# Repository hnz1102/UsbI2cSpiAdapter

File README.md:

# USB-I2C/SPI Adapter

<div align="center">
  
</div>

## Overview

This directory contains the hardware design files for a USB-I2C/SPI adapter based on the FTDI FT232H chip. The adapter enables USB connectivity for I2C and SPI communication with various embedded devices and sensors.

## Hardware Features

- **USB Interface**: USB 2.0 Full Speed (12 Mbps)
- **Main Controller**: FTDI FT232H (MPSSE capable)
- **Protocols Supported**: I2C, SPI, GPIO
- **USB-C Connector**: Modern USB Type-C connection
- **Operating Voltage**: 3.3V I/O (5V USB powered)
- **Compact Design**: Optimized PCB layout for ease of use

## Design Files

This repository includes the following KiCad project files:

| File | Description |
|------|-------------|
| `i2cmaster.kicad_sch` | Schematic design file |
| `i2cmaster.kicad_pcb` | PCB layout file |
| `i2cmaster.kicad_pro` | KiCad project file |
| `i2cmaster.csv` | Bill of Materials (BOM) |
| `fp-lib-table` | Footprint library table |
| `Library.pretty/` | Custom footprint library |

## 3D Model

A 3D model of the enclosure is available:

- `F3D/usbi2c.f3d` - Fusion 360 design file for the adapter enclosure

## Production Files

The `i2cmaster.kicad_pcb_gerber.zip` is Gerber files and production data for PCB manufacturing.

## Key Components

- **FT232H**: FTDI USB-to-MPSSE bridge chip
- **USB-C Connector**: 5077CR-16-SMC2-BK-TR (USB Type-C receptacle)
- **Voltage Regulator**: 3.3V LDO for I/O interface
- **ESD Protection**: Protection circuitry for USB lines
- **Pull-up Resistors**: I2C bus pull-up resistors (typically 4.7kΩ)

## Pin Configuration

The adapter connector has the following pin assignments:

| Pin | Signal | Description |
|-----|--------|-------------|
| 1 | +3.3V | 3.3V power output (limited current) |
| 2 | SCLK/SCL | SPI Clock / I2C Clock |
| 3 | MOSI/SDA | SPI Master Out / I2C Data (OUT in I2C mode) |
| 4 | MISO/SDA | SPI Master In / I2C Data (IN in I2C mode) |
| 5 | CS/DB3 | SPI Chip Select / GPIO DB3 |
| 6 | GND | Ground |
| 7 | GND | Ground |
| 8 | +5V | 5V power output (limited current) |

## DIP Switch Configuration

The adapter includes DIP switches to configure operation mode and pull-up resistors:

| Switch | Position | Function |
|--------|----------|----------|
| S1 | ON | I2C mode (PIN3 and PIN4 connected, PIN3=OUT, PIN4=IN) |
| S1 | OFF | SPI mode (separate MOSI/MISO signals) |
| S2 | ON | SCLK/SCL pull-up resistor enabled |
| S3 | ON | MOSI/SDA pull-up resistor enabled |
| S4 | ON | MISO/SDA pull-up resistor enabled |

**Note**: When S1 is ON (I2C mode), PIN3 and PIN4 are internally connected to form a bidirectional SDA line, with PIN3 functioning as output and PIN4 as input.

## Software Compatibility

This hardware design is compatible with:

- FTDI D2XX drivers (Windows/Linux/macOS)
- libFTDI (open-source alternative)
- Custom applications using MPSSE commands
- Windows GUI application (see [UsbI2cController](https://github.com/hnz1102/UsbI2cController) for software documentation)

## Design Tools

- **KiCad 9.x or later**: PCB design and schematic capture
- **KiCad EDA**: Free and open-source electronics design automation suite

## Opening the Project

1. Install [KiCad](https://www.kicad.org/) (version 9.0 or later recommended)
2. Open the project file: `i2cmaster.kicad_pro`
3. Schematic: Double-click `i2cmaster.kicad_sch`
4. PCB Layout: Double-click `i2cmaster.kicad_pcb`

## Manufacturing

### PCB Specifications

- **Layers**: 2-layer PCB
- **Board Thickness**: 1.6mm (standard)
- **Copper Weight**: 1 oz (35 μm)
- **Surface Finish**: HASL
- **Solder Mask**: Red (or custom color)
- **Silkscreen**: White

## Electrical Characteristics

- **USB Power Input**: 5V ± 5%
- **I/O Voltage Level**: 3.3V CMOS
- **Maximum I/O Current**: Refer to FT232H datasheet
- **I2C Clock Speed**: Up to 400 kHz (Fast Mode) or 3.4 MHz (High-Speed Mode)
- **SPI Clock Speed**: Up to 30 MHz

## License

This Hardware Schematic documents are licensed under CC-BY-SA V4.0.

## References

- [FTDI FT232H Datasheet](https://ftdichip.com/wp-content/uploads/2020/07/DS_FT232H.pdf)
- [FTDI Application Notes](https://ftdichip.com/document/application-notes/)
- [KiCad Documentation](https://docs.kicad.org/)

## Changelog

- **2025-12-26**: Initial hardware design with USB-C connector
- Production files generated for PCB manufacturing

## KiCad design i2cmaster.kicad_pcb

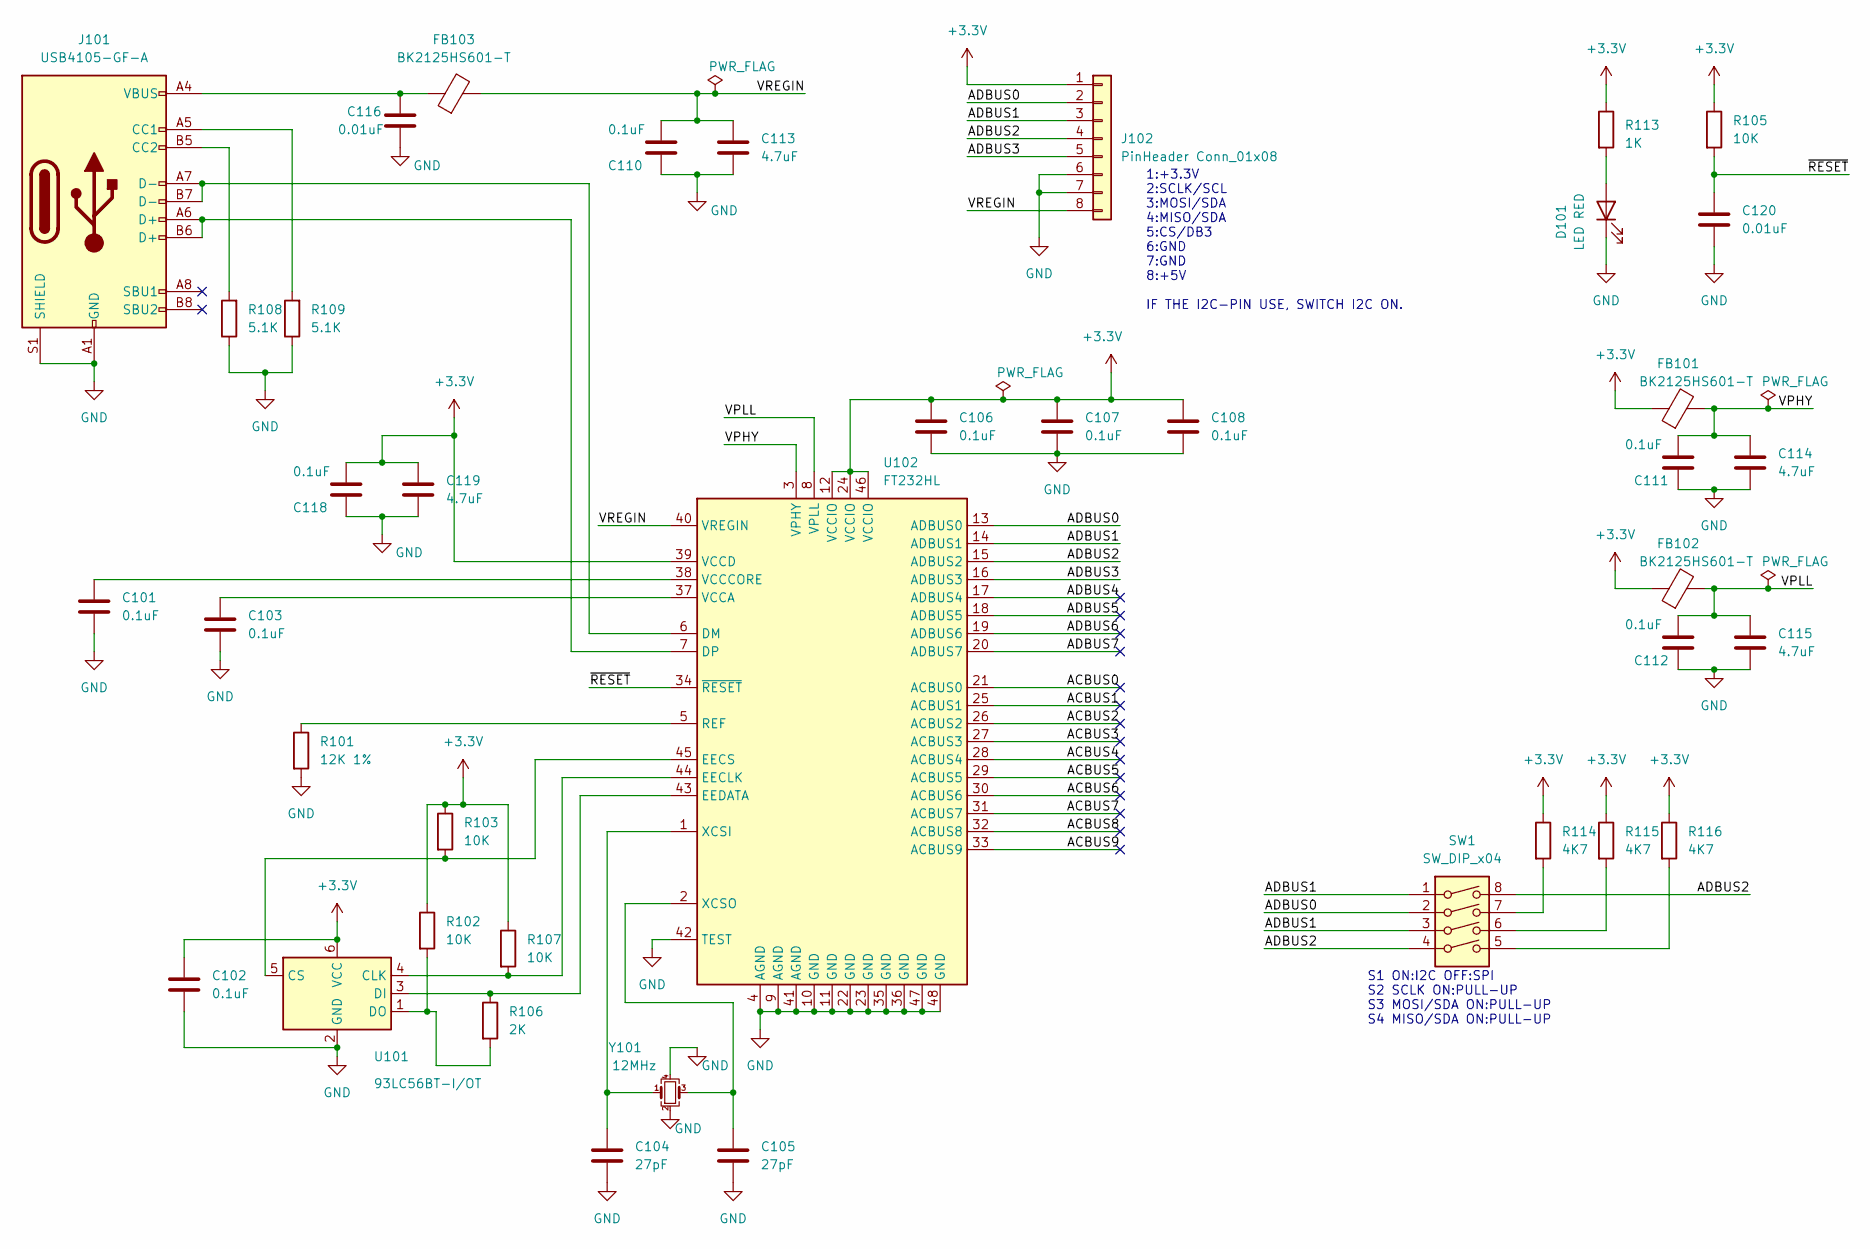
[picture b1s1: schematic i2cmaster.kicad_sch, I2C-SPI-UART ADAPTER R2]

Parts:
C101, C102, C103, C106, C107, C108, C110, C111, C112, C118: 0.1uF; C_0603_1608Metric; digikey 311-1343-1-ND
C104, C105: 27pF; C_0603_1608Metric; digikey 311-1063-1-ND
C113, C114, C115, C119: 4.7uF; C_0805_2012Metric; digikey 490-10751-1-ND
C116, C120: 0.01uF; C_0603_1608Metric; digikey 399-C0603C103K5RACTUCT-ND
D101: LED RED; LED_0603_1608Metric; digikey 3147-B1931URO-20D000114U1930CT-ND
FB101, FB102, FB103: BK2125HS601-T; L_0805_2012Metric_Pad1.15x1.40mm_HandSolder; digikey MH2029-601YCT-ND
J101: USB4105-GF-A; USB_C_5077CR-16-SMC2-BK-TR; digikey 2073-USB4105-GF-ACT-ND
J102: PinHeader Conn_01x08; PinHeader_1x08_P2.54mm_Vertical; digikey 10129379-908001BLF-ND
R101: 12K 1%; R_0603_1608Metric; digikey 13-RC0603FR-1312KLCT-ND
R102, R103, R105, R107: 10K; R_0603_1608Metric; digikey 13-RC0603JR-1010KLCT-ND
R106: 2K; R_0603_1608Metric; digikey 311-2.00KHRCT-ND
R108, R109: 5.1K; R_0603_1608Metric; digikey 311-5.10KHRCT-ND
R113: 1K; R_0603_1608Metric; digikey 13-RC0603JR-1010KLCT-ND
R114, R115, R116: 4K7; R_0603_1608Metric; digikey 311-4.70KHRCT-ND
SW1: SW_DIP_x04; SW_DIP_SPSTx04_Slide_6.7x11.72mm_W7.62mm_P2.54mm_LowProfile; digikey CT2104MS-ND
U101: 93LC56BT-I/OT; SOT-23-6; digikey 93LC56BT-I/OTCT-ND
U102: FT232HL; LQFP-48_7x7mm_P0.5mm; digikey 768-1101-1-ND
Y101: 12MHz; Crystal_SMD_3225-4Pin_3.2x2.5mm; digikey 535-ABM8-272-T3CT-ND

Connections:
+3.3V: C102.1, C106.1, C107.1, C108.1, C118.1, C119.1, FB101.1, FB102.1, J102.1, R102.1, R103.1, R105.1, R107.1, R113.1, R114.1, R115.1, R116.1, U101.6 (VCC), U102.12 (VCCIO), U102.24 (VCCIO), U102.39 (VCCD), U102.46 (VCCIO)
/ACBUS0: U102.21 (ACBUS0)
/ACBUS1: U102.25 (ACBUS1)
/ACBUS2: U102.26 (ACBUS2)
/ACBUS3: U102.27 (ACBUS3)
/ACBUS4: U102.28 (ACBUS4)
/ACBUS5: U102.29 (ACBUS5)
/ACBUS6: U102.30 (ACBUS6)
/ACBUS7: U102.31 (ACBUS7)
/ACBUS8: U102.32 (ACBUS8)
/ACBUS9: U102.33 (ACBUS9)
/ADBUS0: J102.2, SW1.2, U102.13 (ADBUS0)
/ADBUS1: J102.3, SW1.1, SW1.3, U102.14 (ADBUS1)
/ADBUS2: J102.4, SW1.4, SW1.8, U102.15 (ADBUS2)
/ADBUS3: J102.5, U102.16 (ADBUS3)
/ADBUS4: U102.17 (ADBUS4)
/ADBUS5: U102.18 (ADBUS5)
/ADBUS6: U102.19 (ADBUS6)
/ADBUS7: U102.20 (ADBUS7)
/VPHY: C111.1, C114.1, FB101.2, U102.3 (VPHY)
/VPLL: C112.1, C115.1, FB102.2, U102.8 (VPLL)
/VREGIN: C110.1, C113.1, FB103.2, J102.8, U102.40 (VREGIN)
/~RESET: C120.1, R105.2, U102.34 (~RESET)
GND: C101.2, C102.2, C103.2, C104.2, C105.2, C106.2, C107.2, C108.2, C110.2, C111.2, C112.2, C113.2, C114.2, C115.2, C116.2, C118.2, C119.2, C120.2, D101.1 (K), J101.A1 (GND), J101.A12 (GND), J101.B1 (GND), J101.B12 (GND), J101.S1 (SHIELD), J102.6, J102.7, R101.2, R108.1, R109.1, U101.2 (GND), U102.4 (AGND), U102.9 (AGND), U102.10 (GND), U102.11 (GND), U102.22 (GND), U102.23 (GND), U102.35 (GND), U102.36 (GND), U102.41 (AGND), U102.42 (TEST), U102.47 (GND), U102.48 (GND), Y101.2, Y101.4
unnamed: C116.1, FB103.1, J101.A4 (VBUS), J101.A9 (VBUS), J101.B4 (VBUS), J101.B9 (VBUS)
unnamed: D101.2 (A), R113.2
unnamed: J101.A5 (CC1), R109.2
unnamed: J101.B5 (CC2), R108.2
unnamed: R114.2, SW1.7
unnamed: R115.2, SW1.6
unnamed: R116.2, SW1.5
unnamed: R107.2, U101.4 (CLK), U102.44 (EECLK)
unnamed: R103.2, U101.5 (CS), U102.45 (EECS)
unnamed: R106.1, U101.3 (DI), U102.43 (EEDATA)
unnamed: R102.2, R106.2, U101.1 (DO)
unnamed: J101.A7 (D-), J101.B7 (D-), U102.6 (DM)
unnamed: J101.A6 (D+), J101.B6 (D+), U102.7 (DP)
unnamed: R101.1, U102.5 (REF)
unnamed: C103.1, U102.37 (VCCA)
unnamed: C101.1, U102.38 (VCCCORE)
unnamed: C104.1, U102.1 (XCSI), Y101.1
unnamed: C105.1, U102.2 (XCSO), Y101.3

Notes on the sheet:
1:+3.3V 2:SCLK/SCL 3:MOSI/SDA 4:MISO/SDA 5:CS/DB3 6:GND 7:GND 8:+5V IF THE I2C-PIN USE, SWITCH I2C ON.
S1 ON:I2C OFF:SPI S2 SCLK ON:PULL-UP S3 MOSI/SDA ON:PULL-UP S4 MISO/SDA ON:PULL-UP

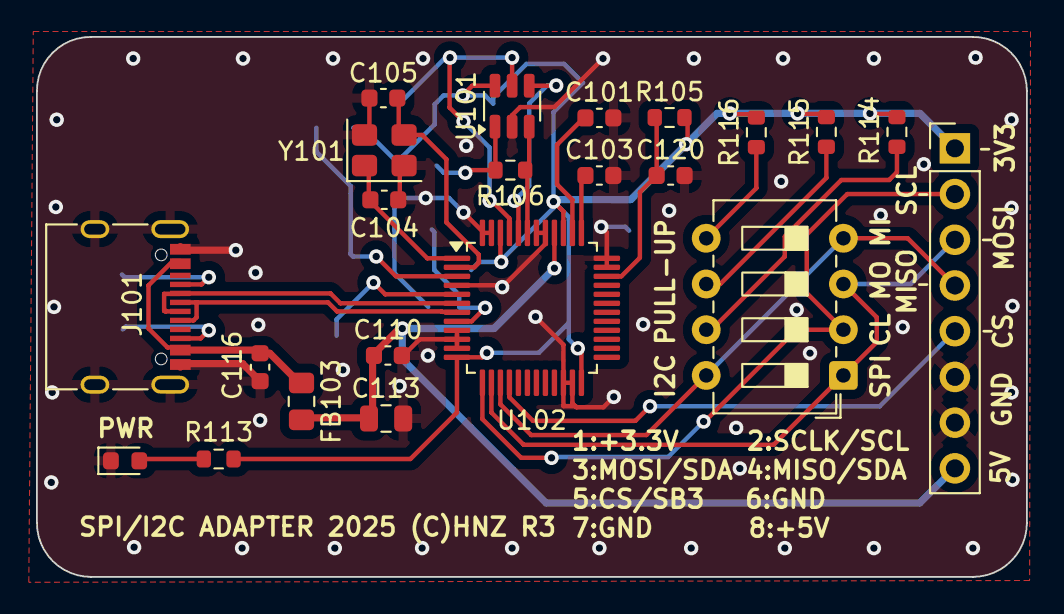
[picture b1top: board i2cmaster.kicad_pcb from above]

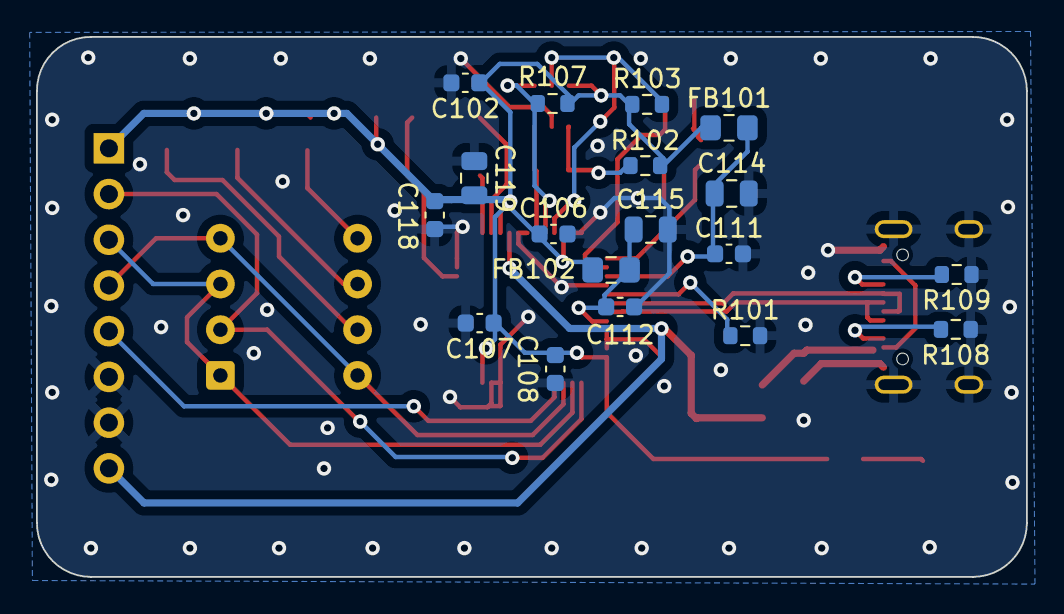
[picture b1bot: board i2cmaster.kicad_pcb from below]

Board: 2 copper layers, 55.0 x 30.0 mm, 40 parts (18 on the bottom side), 28 nets.

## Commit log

2025-12-26 Add enclosure data
2025-12-26 update image
2025-12-26 Add 3MF files
